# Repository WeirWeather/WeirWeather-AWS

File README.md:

# WeirWeather

This repository is for the WeirWeather Automatic Weather Station project which provides live weather measurements from the James Weir buidling in Glasgow, co-ordinates: [55.862809, -4.245339]. This repository contains all of the software, CAD models, BOMs and EAGLE PCB files required to reproduce the weather station and the website.

This project was completed for a Masters group project at the University of Strathclyde Electrical & Electronic Engineering Department. 

WeirWeather - 

- Callum Brooksby
- Zack North
- Mario Manca
- Alexander Ulrichsen
- Tesfu Gebremedhin

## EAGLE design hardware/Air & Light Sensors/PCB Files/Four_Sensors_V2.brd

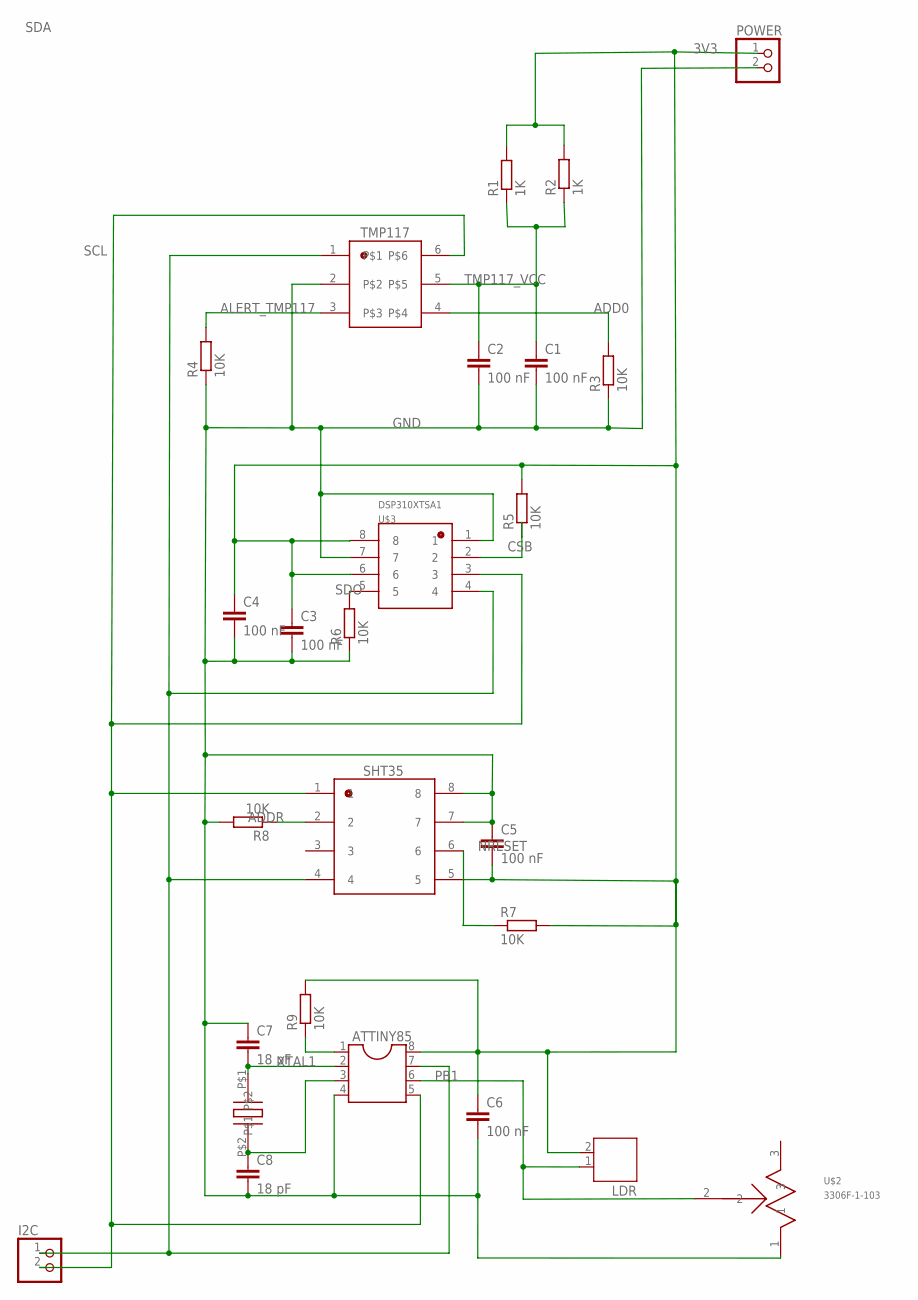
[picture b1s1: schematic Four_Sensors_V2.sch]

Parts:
ATTINY85: DIL8; DIL08
C1, C2, C3, C4, C5, C6: 100 nF; C0603
C7, C8: 18 pF; C0805
I2C: PINHD-1X2; 1X02
LDR: JST-PH2
POWER: PINHD-1X2; 1X02
R1, R2: 1K; R1206
R3, R4, R5, R6, R7, R8, R9: 10K; R0805
SHT35: SHT35
TMP117: TMP117
U$1: QCL16.0000F18B23B
U$2: 3306F-1-103
U$3: DSP310XTSA1

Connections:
3V3: ATTINY85.8, C3.1, C4.1, C5.2, C6.1, LDR.2, POWER.1, R1.2, R2.2, R5.2, R7.2, R9.2, SHT35.5, U$3.6, U$3.8
ADD0: R3.2, TMP117.4
ADDR: R8.1, SHT35.2
ALERT_TMP117: R4.2, TMP117.3
CSB: R5.1, U$3.2
GND: ATTINY85.4, C1.2, C2.2, C3.2, C4.2, C5.1, C6.2, C7.1, C8.2, POWER.2, R3.1, R4.1, R6.1, R8.2, SHT35.7, SHT35.8, TMP117.2, U$2.1, U$3.1, U$3.7
NRESET: R7.1, SHT35.6
PB1: ATTINY85.6, LDR.1, U$2.2
PB5: ATTINY85.1, R9.1
SCL: ATTINY85.7, I2C.1, SHT35.4, TMP117.1, U$3.4
SDA: ATTINY85.5, I2C.2, SHT35.1, TMP117.6, U$3.3
SDO: R6.2, U$3.5
TMP117_VCC: C1.1, C2.1, R1.1, R2.1, TMP117.5
XTAL1: ATTINY85.2, C7.2, U$1.P$1
XTAL2: ATTINY85.3, C8.1, U$1.P$2

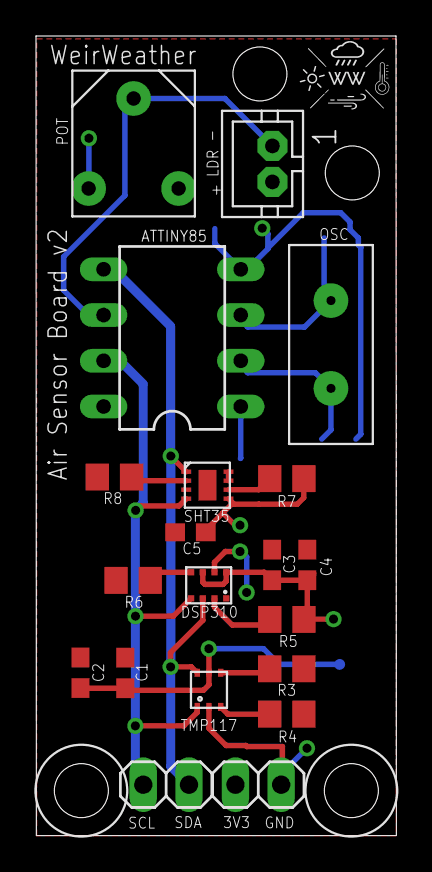
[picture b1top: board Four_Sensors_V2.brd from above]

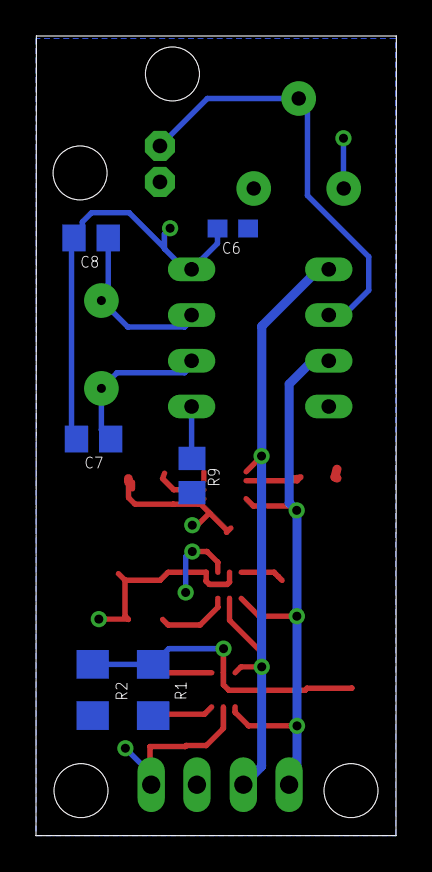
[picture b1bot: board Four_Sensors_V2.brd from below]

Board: 2 copper layers, 20.0 x 44.4 mm, 26 parts (6 on the bottom side), 15 nets.

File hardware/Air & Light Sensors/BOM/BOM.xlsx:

WeirWeather Weather Station
 |  |  |  |  |  |  |  |  | © 2012-2014 Vertex42 LLC
 | Assembly Name : Radiation Shield |  |  |  |  |  |  |  | Bill of Materials Template
 | Assembly Number :
 | Assembly Revision :
 | Approval Date :
 | Part Count : 32.8
 | Total Cost : £ 34.57
Part # | Part Name | Revision | Qty | Units | Supplier | Unit Cost | Cost
1 | TMP117 |  | 1 | each |  | 5.96 | 5.96
2 | 1 KΩ resistor |  | 2 | each |  | 1.2999999999999999E-2 | 2.5999999999999999E-2
3 | 100 nF capacitor |  | 6 | each |  | 0.05 | 0.30000000000000004
4 | 10 KΩ resistor |  | 7 | each |  | 0.01 | 7.0000000000000007E-2
5 | DPS310 |  | 1 | each |  | 1.72 | 1.72
6 | SHT35 |  | 1 | each |  | 8.24 | 8.24
7 | ATtiny85 |  | 1 | each |  | 1.1499999999999999 | 1.1499999999999999
8 | 16 MHz crystal |  | 1 | each |  | 0.17 | 0.17
9 | 18 pF capacitor |  | 2 | each |  | 0.04 | 0.08
10 | 10 KΩ potentiometer |  | 1 | each |  | 0.5 | 0.5
11 | LDR |  | 1 | each |  | 1.89 | 1.89
12 | PCB manufacturing |  | 1 | each |  | 3.06 | 3.06
13 | PETG [Kg] |  | 0.3 | each |  | 24 | 7.1999999999999993
14 | M5 threaded road |  | 0.5 | each |  | 6.37 | 3.1850000000000001
15 | M5 nut |  | 3 | each |  | 0.18 | 0.54
16 | M5 bolt |  | 1 | each |  | 0.18 | 0.18
17 | M5 washer |  | 3 | each |  | 0.1 | 0.30000000000000004
 | Total |  | 32.799999999999997 |  |  |  | 34.570999999999998

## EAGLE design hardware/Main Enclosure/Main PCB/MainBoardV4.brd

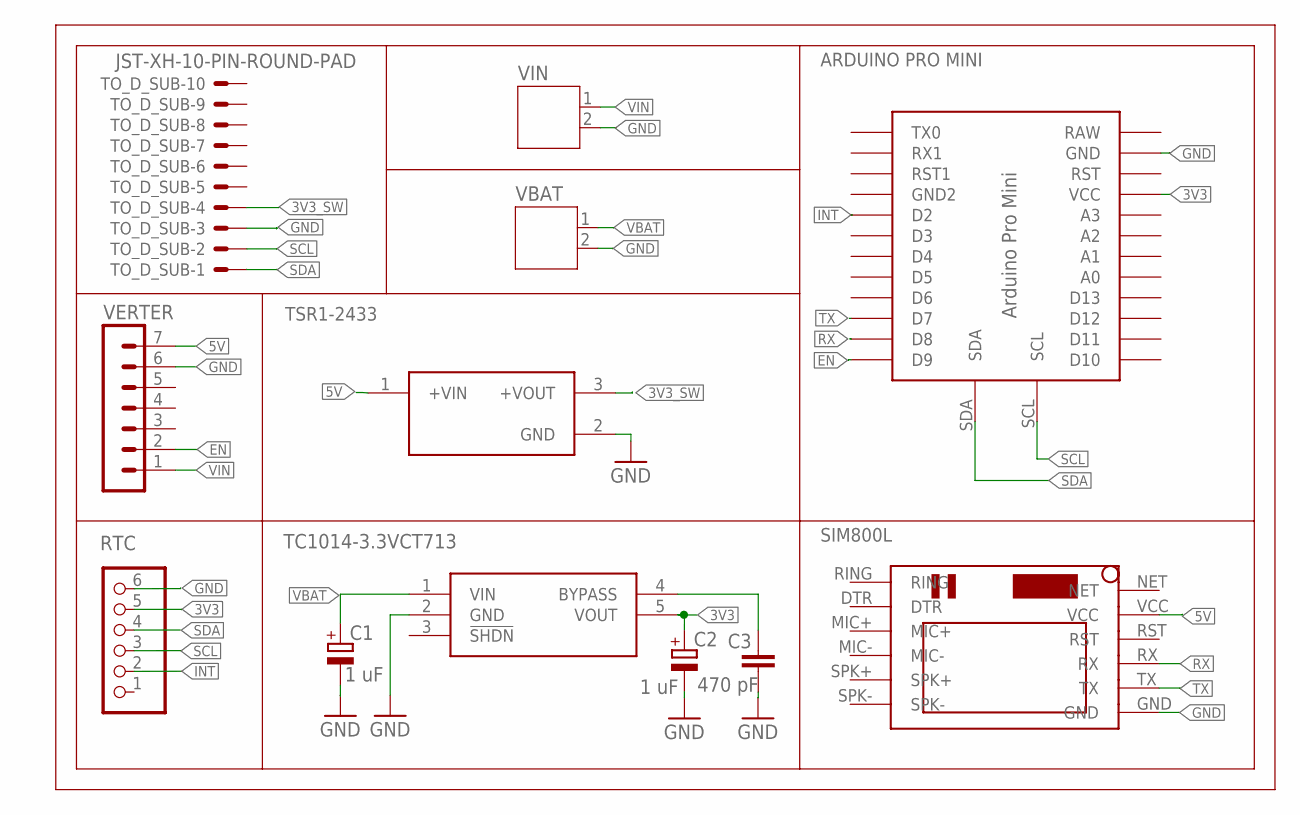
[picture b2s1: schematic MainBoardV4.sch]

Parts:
C1, C2: 1 uF; B/3528-21R
C3: 470 pF; C1206
RTC: PINHD-1X6; 1X06
TO_D_SUB: JST-XH-10-PIN-ROUND-PAD; JST-XH-10-PACKAGE-ROUND-PAD
TSR1-2433: TSR_1-2433; CONV_TSR_1-2433
U1: TC1014-3.3VCT713; SOT95P270X130-5N
U$1: SIM800LMODULE
U$2: ABK-PRO-MINI
VBAT: JST-PH2
VERTER: MA07-1
VIN: JST-PH2

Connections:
3V3: C2.+, RTC.5, U1.5 (VOUT), U$2.VCC
3V3_SW: TO_D_SUB.4, TSR1-2433.3 (+VOUT)
5V: TSR1-2433.1 (+VIN), U$1.VCC, VERTER.7
EN: U$2.D9, VERTER.2
GND: C1.-, C2.-, C3.1, RTC.6, TO_D_SUB.3, TSR1-2433.2 (GND), U1.2 (GND), U$1.GND, U$2.GND, VBAT.2, VERTER.6, VIN.2
INT: RTC.2, U$2.D2
unnamed: C3.2, U1.4 (BYPASS)
RX: U$1.RX, U$2.D8
SCL: RTC.3, TO_D_SUB.2, U$2.SCL
SDA: RTC.4, TO_D_SUB.1, U$2.SDA
TX: U$1.TX, U$2.D7
VBAT: C1.+, U1.1 (VIN), VBAT.1
VIN: VERTER.1, VIN.1

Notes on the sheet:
ARDUINO PRO MINI
SIM800L

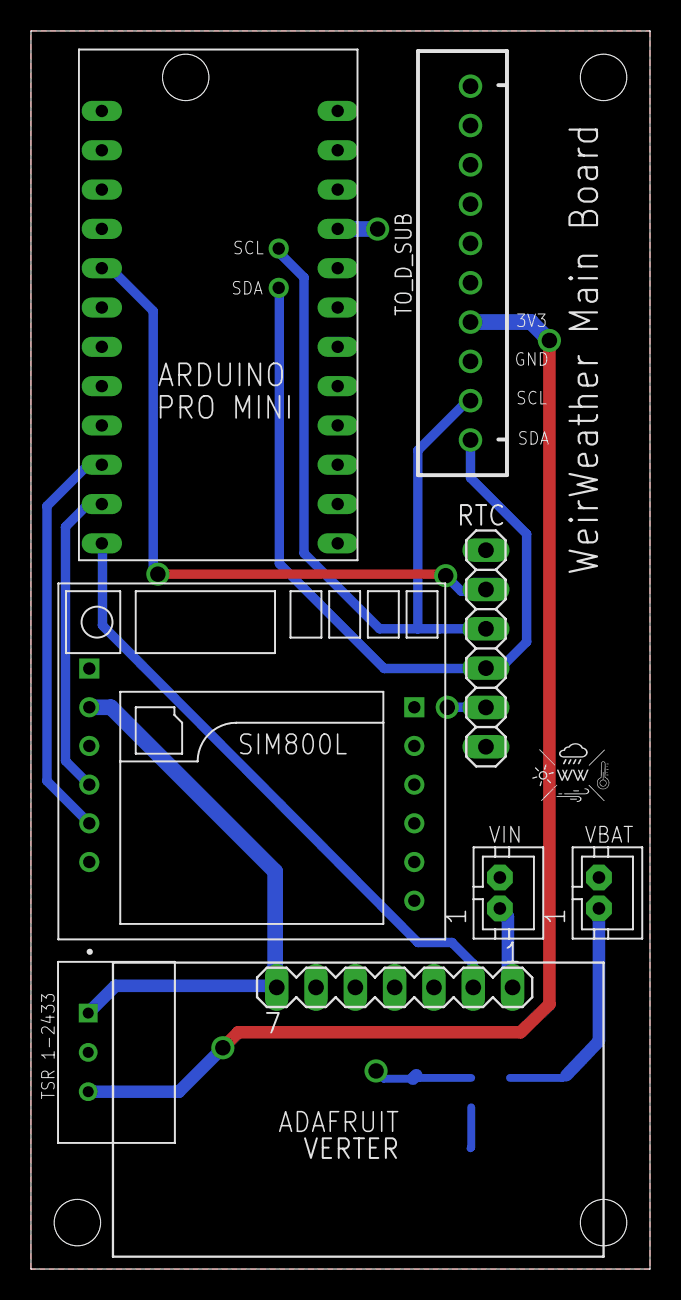
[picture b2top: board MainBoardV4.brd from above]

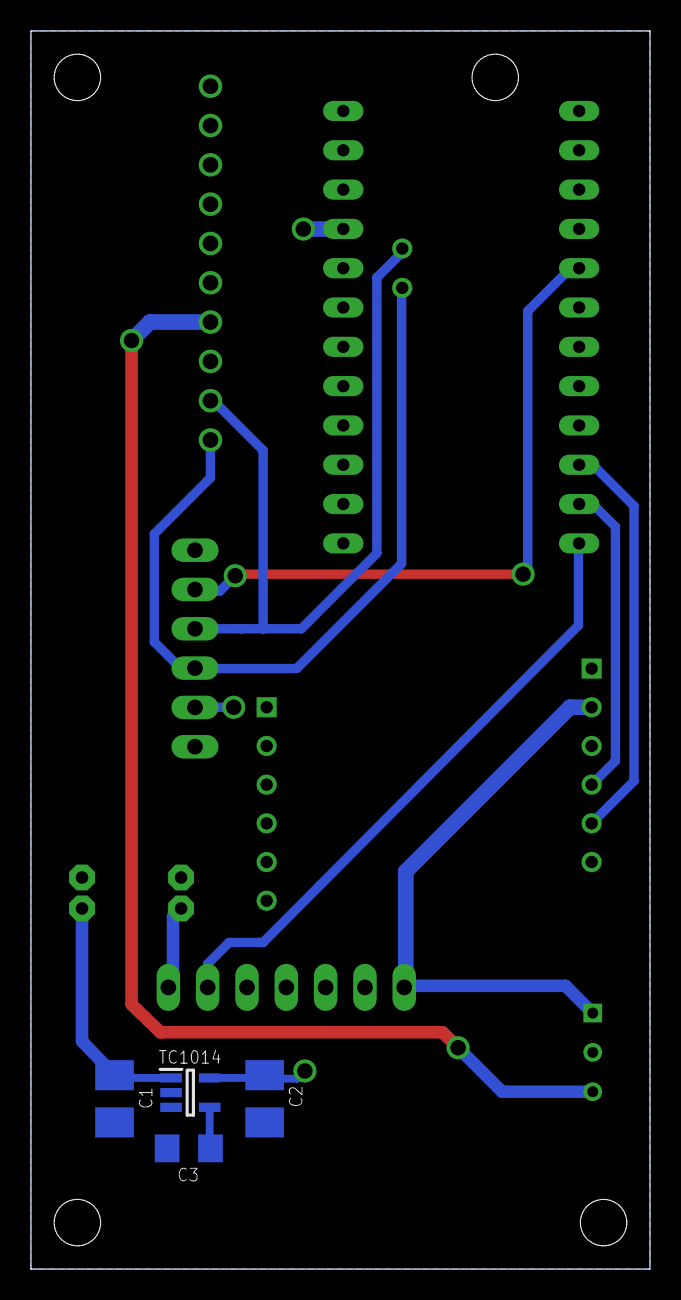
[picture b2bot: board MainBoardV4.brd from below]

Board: 2 copper layers, 40.0 x 80.0 mm, 12 parts (4 on the bottom side), 13 nets.

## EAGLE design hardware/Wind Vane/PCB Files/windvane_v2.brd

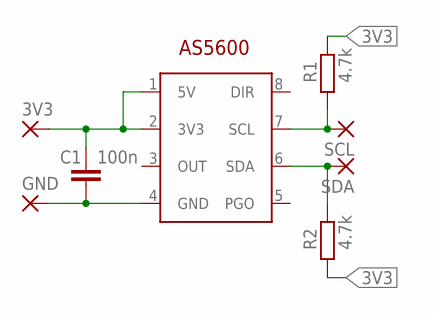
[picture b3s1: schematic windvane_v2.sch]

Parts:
3V3: 1,6/0,8
C1: 100n; C1206
GND: 1,6/0,8
R1, R2: 4.7k; R1206
SCL: 1,6/0,8
SDA: 1,6/0,8
U$1: AS5600; SOIC127P600X175-8N

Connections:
3V3: 3V3.1, C1.1, R1.2, R2.1, U$1.1 (5V), U$1.2 (3V3)
GND: C1.2, GND.1, U$1.4 (GND)
SCL: R1.1, SCL.1, U$1.7 (SCL)
SDA: R2.2, SDA.1, U$1.6 (SDA)

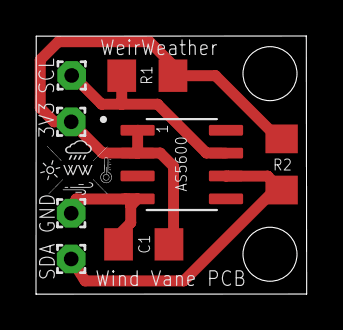
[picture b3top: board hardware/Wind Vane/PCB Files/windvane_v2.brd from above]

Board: 2 copper layers, 15.0 x 14.3 mm, 8 parts (0 on the bottom side), 4 nets.

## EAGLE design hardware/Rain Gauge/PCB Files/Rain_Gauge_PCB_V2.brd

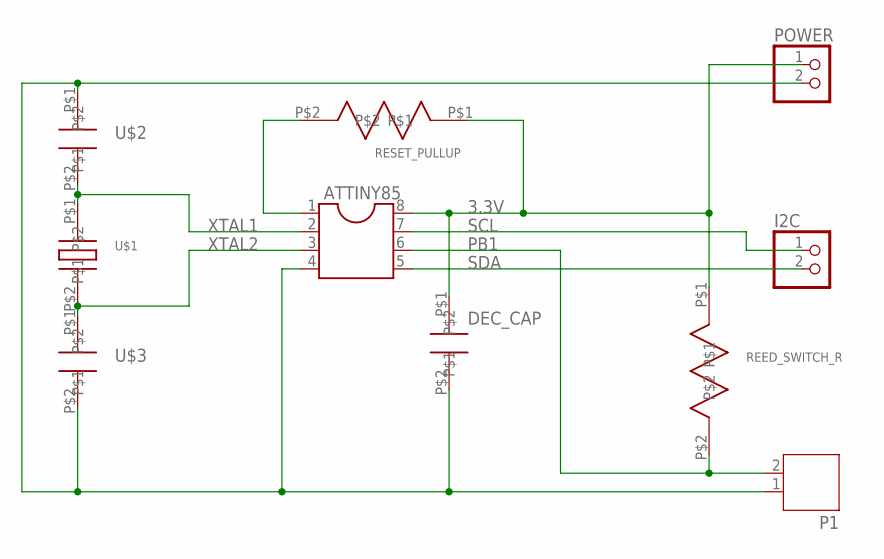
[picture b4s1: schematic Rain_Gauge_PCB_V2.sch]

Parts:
ATTINY85: DIL8; DIL08
DEC_CAP: 0603YC104KAZ2A
I2C: PINHD-1X2; 1X02
P1: JST-PH2
POWER: PINHD-1X2; 1X02
REED_SWITCH_R: RK73B2ATTD103J
RESET_PULLUP: RK73B2ATTD103J
U$1: QCL16.0000F18B23B
U$2, U$3: C0805C180J5GACTU

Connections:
3.3V: ATTINY85.8, DEC_CAP.P$1, POWER.1, REED_SWITCH_R.P$1, RESET_PULLUP.P$1
GND: ATTINY85.4, DEC_CAP.P$2, P1.1, POWER.2, U$2.P$1, U$3.P$2
PB1: ATTINY85.6, P1.2, REED_SWITCH_R.P$2
RESET: ATTINY85.1, RESET_PULLUP.P$2
SCL: ATTINY85.7, I2C.1
SDA: ATTINY85.5, I2C.2
XTAL1: ATTINY85.2, U$1.P$1, U$2.P$2
XTAL2: ATTINY85.3, U$1.P$2, U$3.P$1

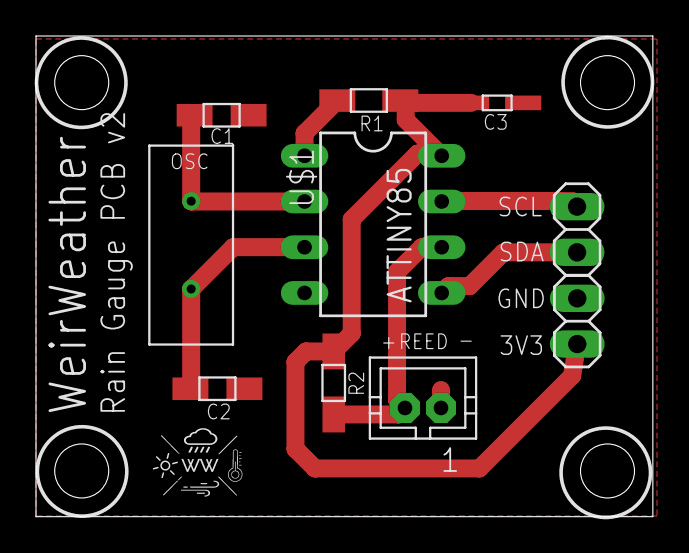
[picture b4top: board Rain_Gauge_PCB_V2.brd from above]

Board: 2 copper layers, 34.3 x 26.7 mm, 10 parts (0 on the bottom side), 8 nets.

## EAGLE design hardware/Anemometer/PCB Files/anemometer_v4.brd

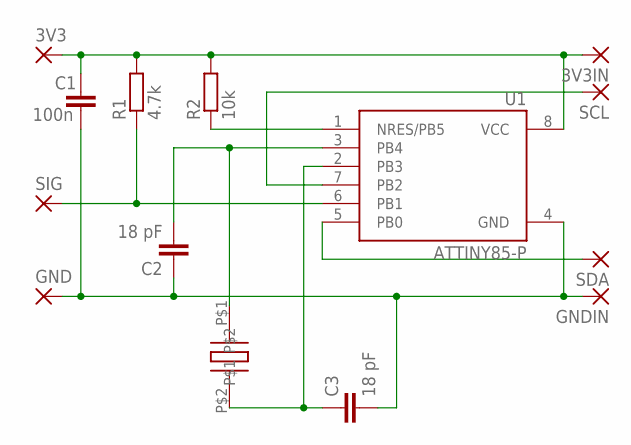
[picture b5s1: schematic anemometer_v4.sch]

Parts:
3V3, 3V3IN: 1,6/0,9
C1: 100n; C1206
C2, C3: 18 pF; C0805
GND: 1,6/0,9
GNDIN: 1,6/0,9
R1: 4.7k; R1206
R2: 10k; R0805
SCL: 1,6/0,9
SDA: 1,6/0,9
SIG: 1,6/0,9
U1: ATTINY85-P; PDIP08_300MIL
U$1: QCL16.0000F18B23B

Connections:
3V3: 3V3.1, 3V3IN.1, C1.1, R1.2, R2.2, U1.8 (VCC)
GND: C1.2, C2.1, C3.2, GND.1, GNDIN.1, U1.4 (GND)
unnamed: SDA.1, U1.5 (PB0)
unnamed: SCL.1, U1.7 (PB2)
unnamed: R1.1, SIG.1, U1.6 (PB1)
unnamed: C2.2, U1.3 (PB4), U$1.P$1
unnamed: C3.1, U1.2 (PB3), U$1.P$2
unnamed: R2.1, U1.1 (NRES/PB5)

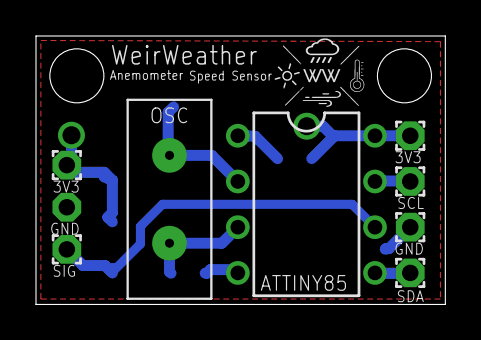
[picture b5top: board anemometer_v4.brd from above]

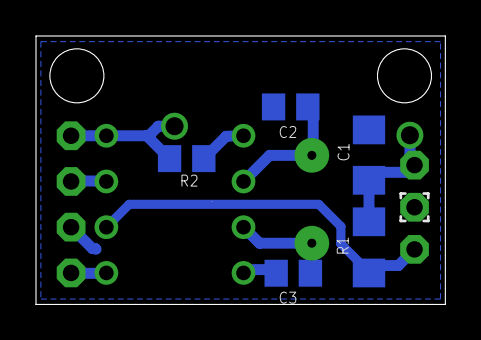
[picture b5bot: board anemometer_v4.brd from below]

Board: 2 copper layers, 22.7 x 14.9 mm, 14 parts (6 on the bottom side), 8 nets.

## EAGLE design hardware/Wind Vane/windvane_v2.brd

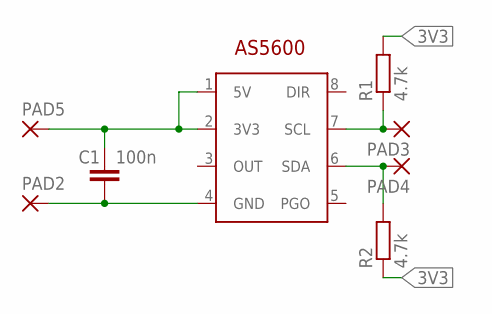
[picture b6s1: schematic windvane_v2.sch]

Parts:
C1: 100n; C1206
PAD2, PAD3, PAD4, PAD5: 1,6/0,8
R1, R2: 4.7k; R1206
U$1: AS5600; SOIC127P600X175-8N

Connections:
3V3: C1.1, PAD5.1, R1.2, R2.1, U$1.1 (5V), U$1.2 (3V3)
GND: C1.2, PAD2.1, U$1.4 (GND)
SCL: PAD3.1, R1.1, U$1.7 (SCL)
SDA: PAD4.1, R2.2, U$1.6 (SDA)

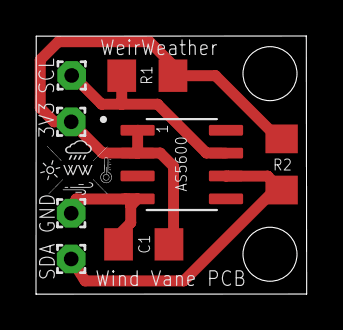
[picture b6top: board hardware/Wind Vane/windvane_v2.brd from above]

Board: 2 copper layers, 15.0 x 14.3 mm, 8 parts (0 on the bottom side), 4 nets.

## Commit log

2020-04-16 Create Photos
2020-04-16 Create doc
2020-04-16 Rain gauge code and README
2020-04-16 Rain gauge README update
2020-04-16 LDR code and README
2020-04-16 Anemometer code and README
2020-04-16 Rain Gauge CAD and STLs files
2020-04-16 Rain Gauge CAD and STLs update
2020-04-16 Rain Gauge CAD README
2020-04-16 Atmospheric sensors CAD and STLs files and README
2020-04-16 Atmospheric sensors README update
2020-04-18 Radiation shield CAD update
2020-04-18 Radiation shield support CAD update
2020-04-19 Radiation shield CAD files update
2020-04-19 Rain Gauge CAD update
2020-04-19 Rain gauge BOM
2020-04-19 Rain gauge photos
2020-04-19 Rain gauge BOM update
2020-04-19 Radiation shield BOM
2020-04-19 Radiation shield photos
2020-04-21 Radiation shield BOM update
2020-04-21 BOMs renamed
2020-04-21 Main enclosure BOM
2020-04-21 Stucture BOM
2020-04-21 Anemometer BOM
2020-04-21 Anemometer STL files
2020-04-21 Wind vane BOM
2020-04-21 Wind vane STL files
2020-04-21 Create Technical Drawings
2020-04-21 Create t
2020-04-21 Create Tech
2020-04-22 BOM update
2020-04-23 Structure BOM update
2020-04-23 Technical drawings
2020-04-23 Anemometer code update
2020-04-24 Final display updates and removal of API key
